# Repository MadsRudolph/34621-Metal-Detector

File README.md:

<div align="center">

# VLF Metal Detector

**Electromagnetic Sensors & Digital Signal Processing**

_A technical implementation of a VLF induction balance metal detector using real-time DFT-based phase detection._

---

</div>

## Overview

This project targets the development of a functional VLF metal detector built on the ATmega328P. It features modular firmware, IIR signal smoothing, and phase-based classification to distinguish between ferromagnetic and non-ferromagnetic metals.

### Features

- **DSP Core:** Single-bin DFT optimized for 4x oversampling (8 kHz) with real-time phase observation.
- **Power Stage:** High-efficiency H-bridge MOSFET driver for the transmitter coil.
- **Coil System:** Concentric coil design with an integrated bucking coil for balance.
- **Feedback:** Real-time OLED HUD and variable-tone buzzer for proximity detection.

## Architecture

```mermaid
graph LR
    MCU[MCU / 2kHz SQ] --> HB[H-Bridge] --> TX[TX Coil]
    Target((Metal)) -. Induction .-> RX[RX Coil]
    RX --> AMP[RX Amp] --> ADC[10-bit ADC]
    ADC --> DFT[DFT Processing] --> IIR[IIR Filter] --> UI[OLED + Buzzer]
```

## Specifications

| Component        | Specification                     |
| :--------------- | :-------------------------------- |
| **TX Frequency** | 2 kHz (Square Wave)               |
| **Sample Rate**  | 8 kHz (4x Oversampling)           |
| **MCU**          | ATmega328P (Arduino Nano @ 16MHz) |
| **Driver**       | H-Bridge (IRF5305 + IRL530)       |
| **Sensors**      | Concentric Coils (Bucking config) |
| **UI**           | SSD1306 OLED (I2C)                |

## Repository

- `Code/` — Core firmware (PlatformIO, C)
- `Docs/` — Technical reports and [Final PDF](Docs/Metaldetektor_Projekt.pdf)
- `KiCad/` — Hardware schematics and PCB designs
- `Simulation/` — LTspice and QSPICE validation files
- `Scripts/` — MATLAB and Python analysis tools

## Getting Started

Build and upload using [PlatformIO](https://platformio.org/):

```bash
cd Code
pio run -t upload
pio device monitor
```

---

<div align="center">
<b>Mads Rudolph · Andreas Skaaning · Jonas Beck · Sigurd Hestbech</b>
<br>
<sub>DTU Course 34621 · January 2026</sub>
</div>

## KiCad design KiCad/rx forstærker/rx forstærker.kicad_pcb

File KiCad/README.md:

# KiCad Skemaer & PCB

Hardware designfiler til VLF Metaldetektoren.

> **Teori:** [Op-Amp Design](obsidian://open?vault=Obsidian&file=Courses%2FIntegrated%20Analog%20Electronics%2FLTspice%20%26%20Kicad%2F02%20-%20Two-Stage%20CMOS%20Op-Amp) | [Induktans](obsidian://open?vault=Obsidian&file=Courses%2FElectromagnetics%2FFormulas%2FL23%20-%20Magnetostatics%20II)

## Status

| Del | Status | Noter |
|-----|--------|-------|
| TX H-bro Driver | ✅ Designet | QSPICE valideret, ~90% effektivitet |
| RX Forstærker | ⏳ Afventer | Design påbegyndt |
| Strømforsyning | ⏳ Afventer | 9V → 5V regulering |
| MCU Sektion | ⏳ Afventer | Arduino Nano breakout |

## Kredsløbsblokke

### 1. Strømforsyning
- 9V batteri input
- Spændingsregulering (5V til MCU)
- Power filtrering
- Batteri monitorering (valgfri)

### 2. TX H-bro Driver
- PWM input fra Arduino (Pin 9)
- **P-kanal MOSFET:** IRF5305PbF (2 stk)
- **N-kanal MOSFET:** IRL530 (2 stk)
- Gate drivere til niveau-skift
- Spoletilslutning (skrueterminal)
- **Effektivitet:** ~90% (QSPICE verificeret)

### 3. RX Forstærker
- Høj-impedans indgangstrin
- Forstærkertrin (op-amp)
- Båndpasfilter omkring 2kHz
- Output skalering til 0-5V for ADC

### 4. Microcontroller Sektion
- Arduino Nano (ATmega328P)
- Intern 10-bit ADC (ingen ekstern ADC nødvendig)
- Timer0 auto-trigger til synkroniseret sampling

### 5. Display & UI
- SSD1306 OLED header (I2C)
- Knapinput (Start/Stop, Kalibrering, Debug)
- Summer output (valgfri)

## Komponentvalg

| Komponent | Delnummer | Pakke | Noter |
|-----------|-----------|-------|-------|
| MCU | Arduino Nano | - | ATmega328P @ 16MHz |
| P-MOSFET | IRF5305PbF | TO-220 | H-bro højside |
| N-MOSFET | IRL530 | TO-220 | H-bro lavside |
| Op-Amp | LM358 / TL072 | DIP-8 | Dual |
| Regulator | 7805 | TO-220 | 5V 1A |
| OLED | SSD1306 | - | 128×64, I2C |

## Pin Mapping (Arduino Nano / ATmega328P)

| Funktion | Arduino Pin | ATmega Pin | Port |
|----------|-------------|------------|------|
| TX Output | 9 | PB1 (15) | PORTB |
| RX Input (ADC) | A0 | PC0 (23) | PORTC |
| I2C SDA | A4 | PC4 (27) | PORTC |
| I2C SCL | A5 | PC5 (28) | PORTC |
| Debug Knap | 4 | PD4 (6) | PORTD |
| Start/Stop | 2 | PD2 (4) | PORTD |
| Kalibrering | 3 | PD3 (5) | PORTD |

## Design Regler (2-lags PCB)

| Parameter | Værdi |
|-----------|-------|
| Min sporbredde | 0.25mm (10mil) |
| Min afstand | 0.25mm (10mil) |
| Via diameter | 0.8mm |
| Via boring | 0.4mm |
| Kobbertykkelse | 1oz |

## Tjekliste

- [x] H-bro design færdigt
- [x] QSPICE simulering bekræftet
- [ ] Skematisk capture komplet
- [ ] ERC (Electrical Rules Check) bestået
- [ ] Footprints tildelt
- [ ] PCB layout komplet
- [ ] DRC (Design Rules Check) bestået
- [ ] Gerbers genereret
- [ ] BOM eksporteret

## Relaterede Dokumenter

- [TX Driver Design.md](../Docs/Theory/TX%20Driver%20Design.md) - H-bro designanalyse
- [Power Budget Analysis.md](../Docs/Theory/Power%20Budget%20Analysis.md) - Strømforbrugsanalyse
- [[../Literature/kravspecifikation.pdf|Kravspecifikation]]

#kicad #pcb #hardware #skema

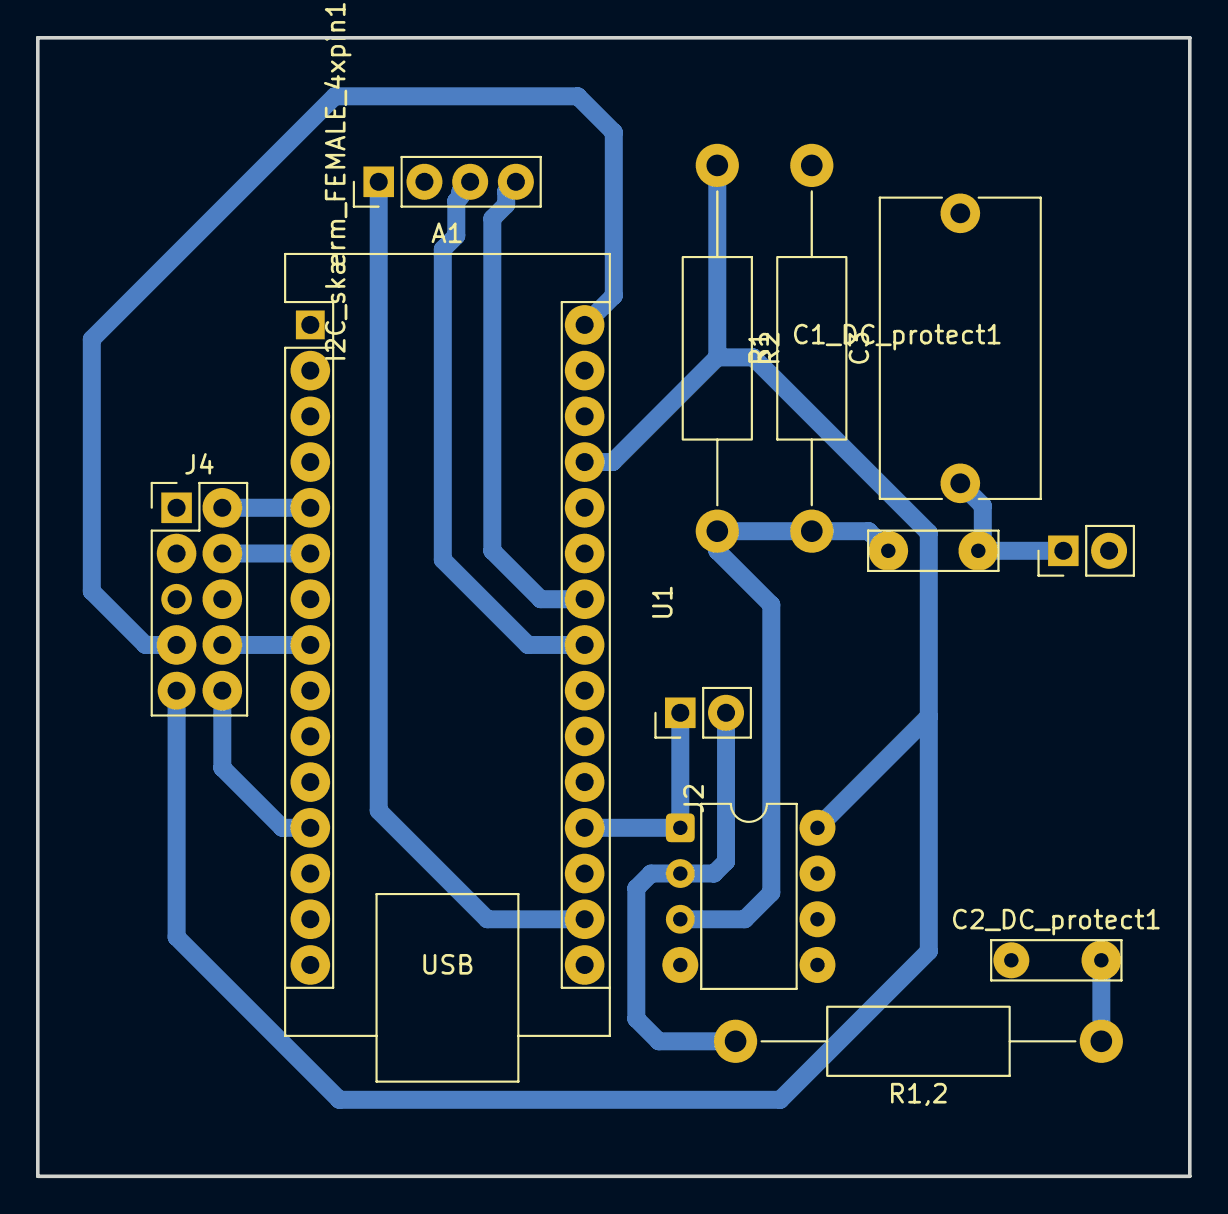
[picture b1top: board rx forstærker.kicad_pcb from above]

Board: 2 copper layers, 64.0 x 63.2 mm, 12 parts (0 on the bottom side), 15 nets.

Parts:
A1: Arduino_Nano
C1_DC_protect1: 1u; C_Rect_L7.0mm_W2.0mm_P5.00mm
C2_DC_protect1: C; C_Rect_L7.0mm_W2.0mm_P5.00mm
C3: 150n; C_Rect_L16.5mm_W8.7mm_P15.00mm_MKT
I2C_skærm_FEMALE_4xpin1: Conn_01x04_Pin; PinHeader_1x04_P2.54mm_Vertical
J1: Rx spole; PinHeader_1x02_P2.54mm_Vertical
J2: Pot_pins_2xpin; PinHeader_1x02_P2.54mm_Vertical
J4: MALE Headers 5xpin; PinHeader_2x05_P2.54mm_Vertical
R1, R2: 100k; R_Axial_DIN0411_L9.9mm_D3.6mm_P20.32mm_Horizontal
R1,2: 1000; R_Axial_DIN0411_L9.9mm_D3.6mm_P20.32mm_Horizontal
U1: MCP6002-xMC; DIP-8_W7.62mm

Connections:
+5V: A1.27 (+5V), J4.9, R2.1, U1.8 (V+)
+9V: A1.30 (VIN), J4.7
/2.5V: C1_DC_protect1.2, R1.1, R2.2, U1.3
/Kalibrering: A1.6 (D3), J4.4
/PA_power_off: A1.8 (D5), J4.8
/Rx_ADC: A1.19 (A0), J2.1, U1.1
/SCL: A1.24 (A5), I2C_skærm_FEMALE_4xpin1.4
/SDA: A1.23 (A4), I2C_skærm_FEMALE_4xpin1.3
/Start/Stop: A1.5 (D2), J4.2
/TX_out->PA: A1.12 (D9), J4.10
/Vin: A1.17 (3V3), I2C_skærm_FEMALE_4xpin1.1
/rx spole. 12.225mH og 71 ohm: C1_DC_protect1.1, C3.1, J1.1
GND: A1.4 (GND), A1.29 (GND), C2_DC_protect1.1, C3.2, I2C_skærm_FEMALE_4xpin1.2, J4.1, J4.3, R1.2, U1.4 (V-)
unnamed: C2_DC_protect1.2, R1,2.1
unnamed: J2.2, R1,2.2, U1.2

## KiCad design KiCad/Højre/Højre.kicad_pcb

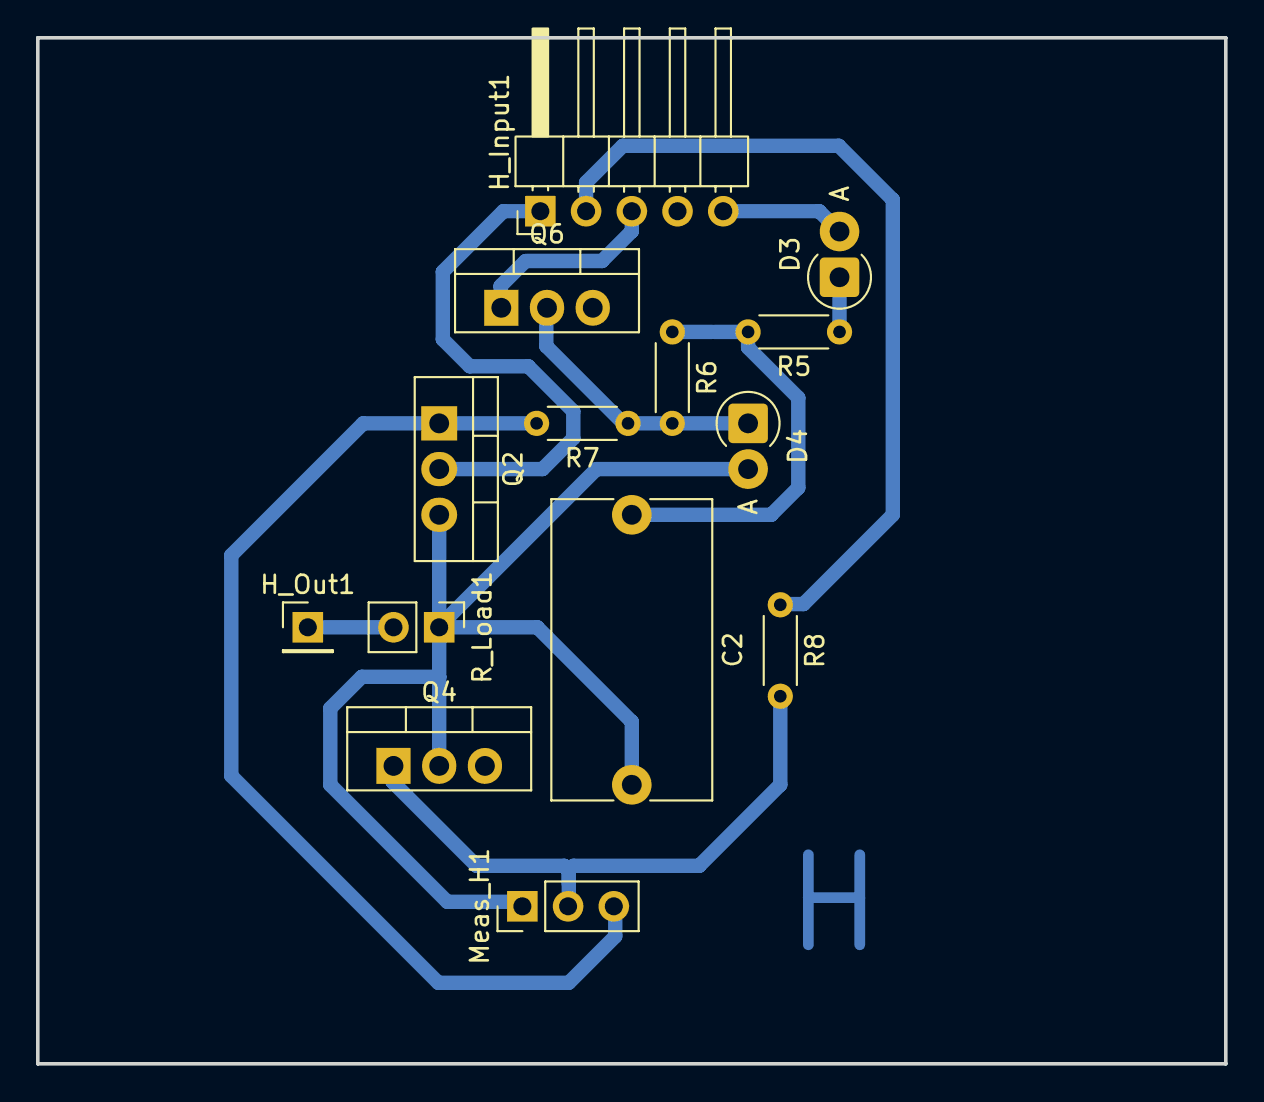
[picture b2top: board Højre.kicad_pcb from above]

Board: 2 copper layers, 66.0 x 57.0 mm, 14 parts (0 on the bottom side), 12 nets.

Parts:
C2: 820n; C_Rect_L16.5mm_W8.7mm_P15.00mm_MKT
D3, D4: D; D_DO-41_SOD81_P2.54mm_Vertical_AnodeUp
H_Input1: Conn_01x05_Pin; PinHeader_1x05_P2.54mm_Horizontal
H_Out1: Conn_01x01_Pin; PinHeader_1x01_P2.54mm_Vertical
Meas_H1: Conn_01x03_Pin; PinHeader_1x03_P2.54mm_Vertical
Q2, Q4, Q6: NMOS_IRL530; TO-220-3_Vertical
R5, R7, R8: 1; R_Axial_DIN0204_L3.6mm_D1.6mm_P5.08mm_Horizontal
R6: 1k; R_Axial_DIN0204_L3.6mm_D1.6mm_P5.08mm_Horizontal
R_Load1: 47; PinHeader_1x02_P2.54mm_Vertical

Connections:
+5V: D3.2 (A), H_Input1.5
+9V: H_Input1.1, Q2.2 (G)
/Meas_GATE_M2: Meas_H1.3, Q2.1 (D), R7.2
/Meas_GATE_M4: Meas_H1.2, Q4.1 (D), R8.2
/Meas_H_Out: C2.2, D4.2 (A), Meas_H1.1, Q2.3 (S), Q4.2 (G), R_Load1.1
/PWM1_NOT: H_Input1.3, Q6.1 (D)
/PWM2: H_Input1.2, R8.1
GND: H_Input1.4, Q4.3 (S), Q6.3 (S)
unnamed: C2.1, R5.2, R6.1
unnamed: D3.1 (K), R5.1
unnamed: D4.1 (K), Q6.2 (G), R6.2, R7.1
unnamed: H_Out1.1, R_Load1.2

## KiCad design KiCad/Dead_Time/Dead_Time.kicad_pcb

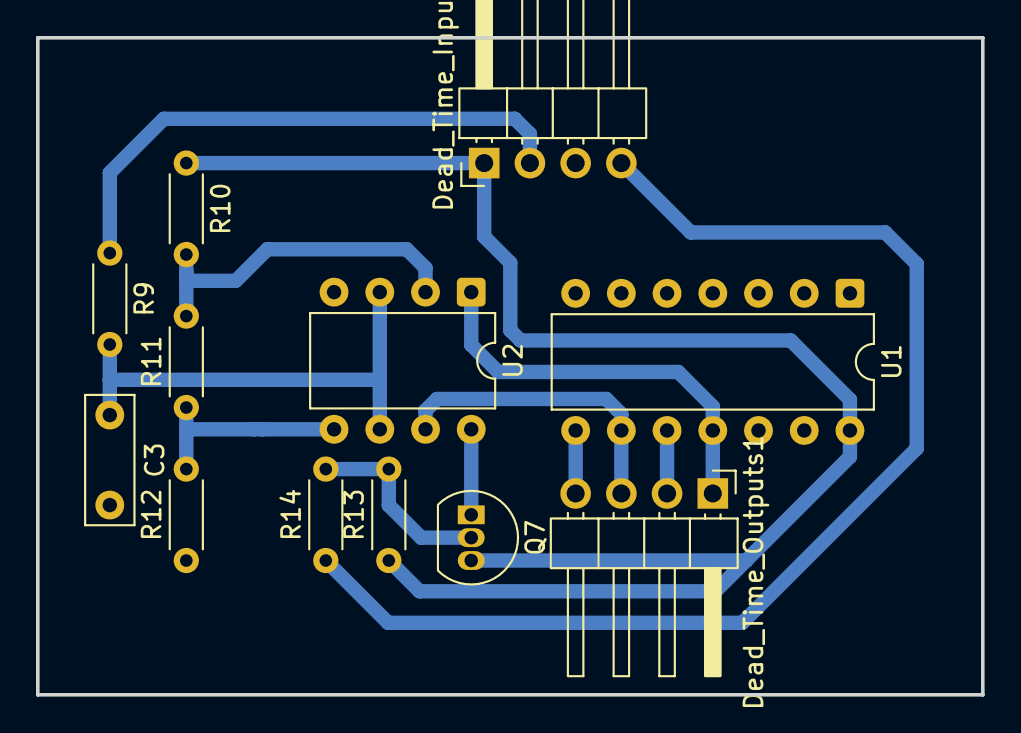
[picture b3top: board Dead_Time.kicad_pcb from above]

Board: 2 copper layers, 52.5 x 36.5 mm, 12 parts (0 on the bottom side), 13 nets.

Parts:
C3: 4n8; C_Rect_L7.0mm_W2.5mm_P5.00mm
Dead_Time_Inputs1: Conn_01x04_Pin; PinHeader_1x04_P2.54mm_Horizontal
Dead_Time_Outputs1: Conn_01x04_Pin; PinHeader_1x04_P2.54mm_Horizontal
Q7: PNP_BC558; TO-92_Inline
R9: 15k; R_Axial_DIN0204_L3.6mm_D1.6mm_P5.08mm_Horizontal
R10, R12: 2k25; R_Axial_DIN0204_L3.6mm_D1.6mm_P5.08mm_Horizontal
R11: 500; R_Axial_DIN0204_L3.6mm_D1.6mm_P5.08mm_Horizontal
R13: 10k; R_Axial_DIN0204_L3.6mm_D1.6mm_P5.08mm_Horizontal
R14: 1k; R_Axial_DIN0204_L3.6mm_D1.6mm_P5.08mm_Horizontal
U1: 74AUC2G04; DIP-14_W7.62mm
U2: MCP6002; DIP-8_W7.62mm

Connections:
+5V: Dead_Time_Inputs1.1, Q7.3 (E), R10.1, R13.1, U1.14
/KILL_SWITCH: Q7.1 (C), U2.8 (V+)
/Meas_VStep1: R10.2, R11.2, U2.2 (-)
/Meas_VStep2: R11.1, R12.2, U2.5 (+)
/PWM1: Dead_Time_Outputs1.1, U1.11, U2.1
/PWM1_NOT: Dead_Time_Outputs1.2, U1.10
/PWM2: Dead_Time_Outputs1.3, U1.9, U2.7
/PWM2_NOT: Dead_Time_Outputs1.4, U1.8
/PWM_In: Dead_Time_Inputs1.2, R9.1
/on/off: Dead_Time_Inputs1.4, R14.1
GND: C3.2, Dead_Time_Inputs1.3, R12.1, U1.7, U2.4 (V-)
unnamed: Q7.2 (B), R13.2, R14.2
unnamed: C3.1, R9.2, U2.3 (+), U2.6 (-)

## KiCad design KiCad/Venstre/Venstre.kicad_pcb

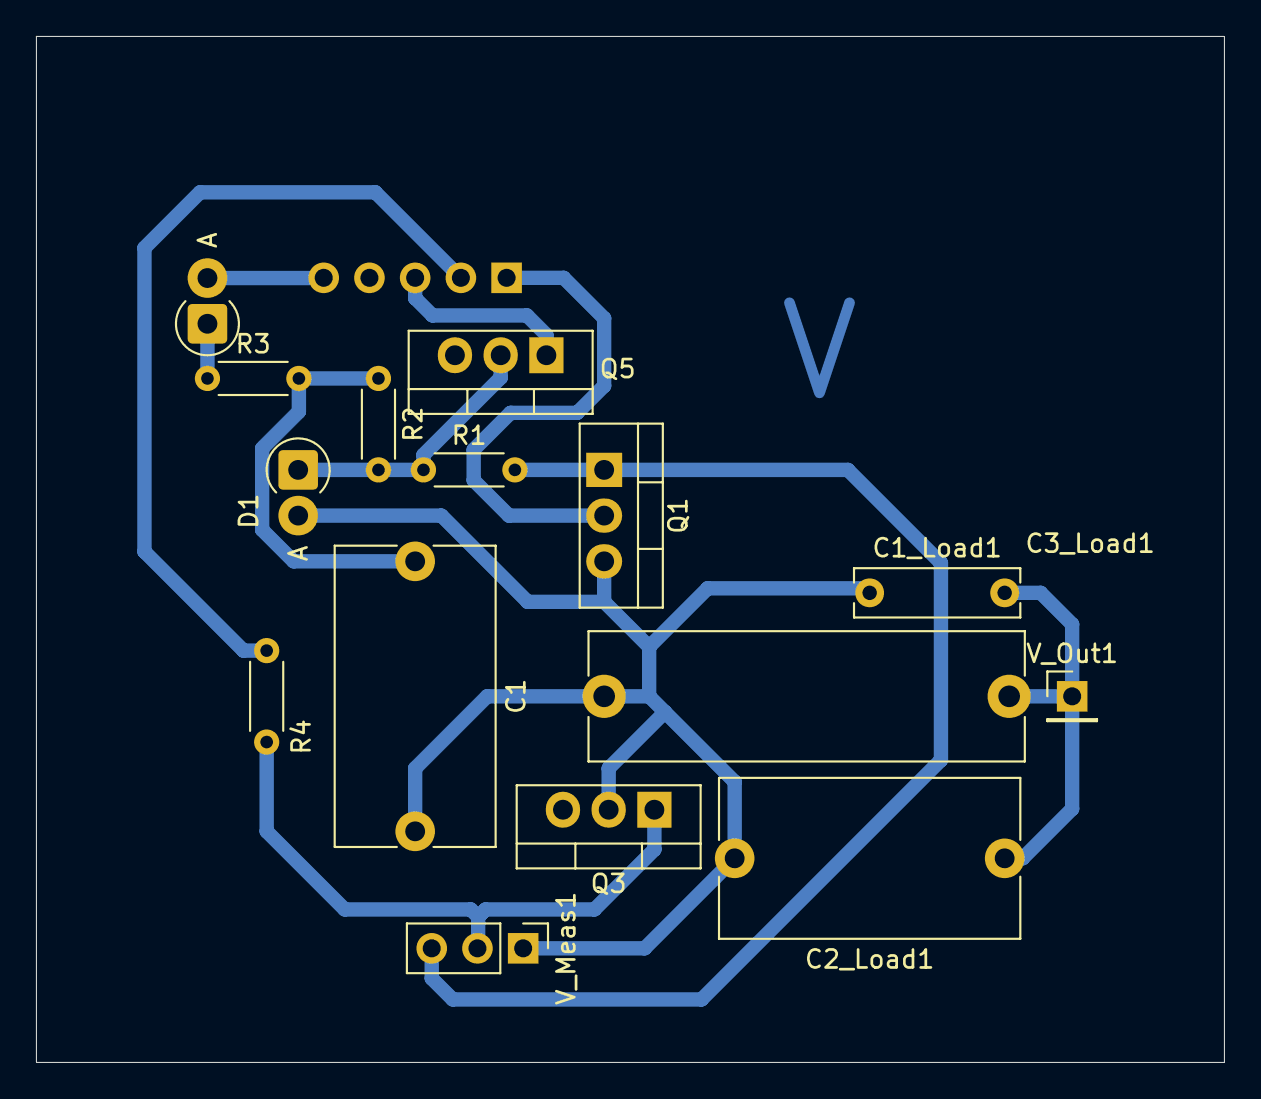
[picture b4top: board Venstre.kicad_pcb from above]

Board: 2 copper layers, 66.0 x 57.0 mm, 16 parts (1 on the bottom side), 12 nets.

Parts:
C1, C2_Load1: 820n; C_Rect_L16.5mm_W8.7mm_P15.00mm_MKT
C1_Load1: 100n; C_Rect_L9.0mm_W2.5mm_P7.50mm_MKT
C3_Load1: 2u2; C_Rect_L24.0mm_W7.0mm_P22.50mm_MKT
D1, D2: D; D_DO-41_SOD81_P2.54mm_Vertical_AnodeUp
Q1, Q3, Q5: NMOS_IRL530; TO-220-3_Vertical
R1, R3, R4: 1; R_Axial_DIN0204_L3.6mm_D1.6mm_P5.08mm_Horizontal
R2: 1k; R_Axial_DIN0204_L3.6mm_D1.6mm_P5.08mm_Horizontal
V_Inputs1: Conn_01x05_Pin; PinHeader_1x05_P2.54mm_Horizontal
V_Meas1: Conn_01x03_Pin; PinHeader_1x03_P2.54mm_Vertical
V_Out1: Conn_01x01_Pin; PinHeader_1x01_P2.54mm_Vertical

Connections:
+5V: D2.2 (A), V_Inputs1.5
+9V: Q1.2 (G), V_Inputs1.1
/Meas_GATE_M1: Q1.1 (D), R1.2, V_Meas1.3
/Meas_GATE_M3: Q3.1 (D), R4.2, V_Meas1.2
/Meas_V_Out: C1.2, C1_Load1.1, C2_Load1.2, C3_Load1.1, D1.2 (A), Q1.3 (S), Q3.2 (G), V_Meas1.1
/PWM1: R4.1, V_Inputs1.2
/PWM2_NOT: Q5.1 (D), V_Inputs1.3
GND: Q3.3 (S), Q5.3 (S), V_Inputs1.4
unnamed: C1.1, R2.1, R3.2
unnamed: D1.1 (K), Q5.2 (G), R1.1, R2.2
unnamed: D2.1 (K), R3.1
unnamed: C1_Load1.2, C2_Load1.1, C3_Load1.2, V_Out1.1

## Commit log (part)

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2026-01-05 Initial commit: VLF Metal Detector project
2026-01-05 added crosslink to DTU Obsidian Vault
2026-01-06 ingenting
2026-01-06 added maple
2026-01-06 Created power_test.c to test current draw on Arduino Mega
2026-01-06 Lavet lidt udregner i Maple, de skal kigges mere på
2026-01-07 Simplify to prime number calculator test program
    Replace complex metal detector firmware with simple prime calculator
    that displays results on OLED. Removes unused DSP, sampling, TX, and
    UART modules to measure baseline power consumption.
2026-01-07 Mutual inductance added
2026-01-07 B-fields added
2026-01-07 Power Budget code works, documented findings and updated power budget analysis.md, preparing to merge back into main branch
2026-01-07 Add power_test directory with power budget test code
    Merged code from Powerbudget branch as a separate directory to allow
    running power consumption tests independently from the main detector code.
    Includes Power Budget Analysis documentation.
2026-01-07 made a plan for code execution, and updated Power budget analysis
2026-01-07 Skabelon til coiludregninger
2026-01-07 Update .gitignore and untrack generated files
    Remove workspace.json, nested .vscode folders, .claude settings, and
    build artifacts from tracking to prevent merge conflicts when switching
    branches. These files are machine/user-specific and shouldn't be shared.
2026-01-07 Add debug system and complete firmware implementation
    Debug System:
    - debug.h/debug.c: 4-screen diagnostic system (ADC, DFT Accum, DFT Result, Timing)
    - Integer math: isqrt(), fast_atan2_deg() for embedded constraints
    - Pin 13 toggle for oscilloscope timing verification
    - Activate by holding both buttons in IDLE state
    Firmware:
2026-01-08 Add Arduino Nano (ATmega328P) support
    Implement portable firmware supporting both Arduino Mega 2560 and Nano:
    - config.h: Board detection with conditional pin/timer definitions
    - tx.c: Use config macros for TX PWM pin (PB5 on Mega, PB1 on Nano)
    - ui.c: Timer4 (Mega) / Timer2 (Nano) buzzer, portable button handling
    - main.c: Use BTN_PIN macros for button reading
    - debug.h/c: Include config.h for debug pin (PB7 on Mega, PB0 on Nano)
2026-01-08 QSPICE sim virker ca 90% effektiv
2026-01-08 Created matlab simulation of coil design
2026-01-08 opdateret maple
2026-01-08 referat fra møde 8-1-26
2026-01-08 Timer 0
2026-01-09 Port migration branch logic with bug fixes applied
    - Simplified DSP/TX code using migration branch style
    - Fixed OCR0A: 124 -> 249 for correct 8kHz interrupt rate
    - Fixed types: xn as int16_t for signed DC offset result
    - Replaced floating-point sqrt/atan2 with integer-only versions
    - Using auto-trigger ADC (ADATE) instead of manual triggering
    - Added proper header declarations and function prototypes
2026-01-09 made a simple test program with everything in main.c no sub .c documents or header files
2026-01-09 simple main is now the main code branch
2026-01-09 fixede timer0
2026-01-09 📝 Add docstrings to `simplemain`
    Docstrings generation was requested by @MadsRudolph.
    * https://github.com/MadsRudolph/34621-Metal-Detector/pull/11#issuecomment-3730168718
    The following files were modified:
    * `Code/src/drivers/I2C.c`
    * `Code/src/main.c`
2026-01-09 Add Coil Configuration Comparison from Powerbudget branch
2026-01-09 Add Maple coil design document
2026-01-09 Reorganize documentation: new Docs/ structure, delete outdated files
    - Created Docs/Guides, Docs/Theory, Docs/Meetings, Docs/Templates
    - Moved all documentation to appropriate folders
    - Deleted outdated: Debug_Guide.md, Development Roadmap.md, Search Coil Design.md
    - Renamed Coil_Design_Reconciliation.md to Coil Design.md
    - Updated Home.md with new links and current architecture
2026-01-10 Major documentation overhaul and firmware cleanup
    Project Roadmap & Requirements:
    - Add Project_Roadmap.md with full requirements analysis (16 krav)
    - Map implementation status: ~45% complete (SW 70%, HW 30%)
    - Document outstanding tasks, risks, and test checklist
    Firmware (main.c):
    - Restructure with clear section headers and organization
2026-01-10 Add push-pull driver design and efficiency analysis to TX Driver docs
    - Add new push-pull (totem-pole) driver circuit with 5 BJTs
    - Add ASCII schematics and component list for push-pull design
    - Add H-bridge vs push-pull comparison table
    - Add efficiency and battery consumption analysis section
    - Add detailed battery life calculations (174 min vs 271 min)
    - Add build instructions, wiring guide, and test procedures
2026-01-10 Add report export system for Overleaf integration
    - Report_Export/ folder for staging assets (figures, schematics, code, data)
    - export_to_report.sh script to sync assets to report repository
    - README with workflow and naming conventions
2026-01-11 Hbro done 98% effektivitet
2026-01-11 opdateret RLC filter som giver pæn sinus
2026-01-12 Add QSPICE simulation documentation
    Document the H-bridge TX driver simulation files:
    - Hbro_sim.qsch: Main H-bridge with IRL530 MOSFETs and LC tank (~98% efficiency)
    - bootstrap.qsch: Bootstrap gate driver for high-side N-channel drive
    - dead_time.qsch: RC-based dead-time generator using op-amp comparators
    Includes circuit topology, component specifications, operating principles,
    and simulation commands for parameter sweeps.
2026-01-12 Address review comments for QSPICE documentation
    - Add 'text' language specifier to ASCII diagram code blocks for
    proper markdown rendering
    - Document R4/R8 (1K) pull-up resistors in Bootstrap Components table
    - Add explanation for pull-up resistor function
2026-01-12 Consolidate and restructure documentation
    Documentation reduced from 18 to 14 files by merging redundant content:
    New files:
    - Docs/Guides/Testing Guide.md - Unified test guide (AD3, RC Loopback, MATLAB DFT)
    - Docs/Theory/TX Driver Design.md - H-bridge driver theory
    Merged and deleted:
    - Coil Configuration Comparison.md -> merged into Coil Design.md
2026-01-12 Add coil winder project and documentation
    - Add complete coil winder firmware with Doxygen documentation
    - ATmega328P-based controller for automated coil winding
    - Servo-controlled wire guide with encoder feedback
    - SSD1306 OLED display interface
    - Configurable coil presets for TX/RX coils
    - 3D printable mechanical parts (OpenSCAD)
2026-01-13 Replace ITR8307 reflective sensor with break-beam optical sensor
    - New sensor design using SFH4546 IR emitter + BP104 photodiode + LM311 comparator
    - All components available from DTU component shop
    - More reliable detection using slotted encoder disc instead of reflective stripe
    - Updated circuit schematics, component calculations, and wiring diagrams
    - Added DTU component shop inventory CSV for reference
2026-01-13 Fix Wheeler inductance formula and update coil design documentation
    - Fix Wheeler formula coefficient: 0.8 (inches) -> 0.315 (cm)
    - Add single-layer Wheeler formula for bucking coil
    - Add geometry warning for flat TX coil
    - Update MATLAB script with verified formulas
    - Update coil specifications based on corrected calculations
    - Update power budget for 360mA TX current
2026-01-15 Enkelte QSPICE ændringer plus kicad schematik af Hbro
2026-01-15 ændret kicad opsætning
2026-01-15 Update Coil Design with measured values
    - TX+Bucking series: 2.03 mH (vs 5.82 mH theoretical)
    - RX inductance: 12.25 mH (0.4% error from theory)
    - Bucking coil optimal: 20 turns (removed 15 from 35)
2026-01-15 Update coil specs with verified measurements from verify_coils.m
    Actual specifications:
    - TX: 70 turns, 2 layers, 200mm, 0.56mm wire → 1.97 mH
    - Bucking: 20 turns, 1 layer, 60mm, 0.56mm wire → 0.038 mH
    - RX: 445 turns, 3 layers, 50mm, 0.15mm wire → 11.1 mH
    Verification results:
    - TX+Bucking: 2.01 mH theoretical vs 2.03 mH measured (-0.9% error)
2026-01-15 Update coil design with prototype simulation values
    - TX: 70 turns, 2 layers, 1.97 mH, 3.02Ω DC
    - RX: 445 turns, 3 layers, 11.15 mH, 67.05Ω DC
    - Bucking: 20 turns calibrated, 0.04 mH, 0.26Ω DC
    - Updated resonance calculations and overview tables
    - MATLAB script now uses actual prototype values
2026-01-16 nyste pcb design til AP forstærker
2026-01-16 alla pcber er klar til routing
2026-01-16 deadtime pcb almost done, missing 1 gnd connection
2026-01-16 Venstre og Højre pcb klar til produktion
2026-01-16 midlertidig backup før branch skift
2026-01-17 niger
2026-01-17 pcb layouts done
2026-01-17 Remove Doxygen-generated HTML documentation
    Delete auto-generated documentation files from Code/docs/html
    and coil_winder/docs/html directories.
2026-01-17 Add tmpclaude-* to gitignore
2026-01-17 Re-enable MATLAB capture code
2026-01-18 sleep + rx forstærker i LT
2026-01-18 RX forstærker + MCU i kicad, mangler footprints
2026-01-18 rxforstærker simplificeret
2026-01-18 Modulariser kode og tilføj buzzer feedback
    Opdeler main.c i separate moduler for bedre læsbarhed:
    - config.h: Alle konfigurationskonstanter
    - timer: TX signal generation og sleep mode
    - adc: 8kHz ADC sampling
    - button: Knap håndtering
    - dft: DFT beregning
2026-01-19 Ret metal klassificering og tilføj sleep pin styring
    - Ret ferro/non-ferro klassificering (positiv fase = ferro, negativ = non-ferro)
    - Sænk magnitude tærskel for bedre følsomhed (20% eller +3)
    - Tilføj SLEEP_PIN (PD5) til at styre forstærker sleep mode
    - Gør signal bar mere følsom (bar_max 200 → 50)
2026-01-19 Add graphical HUD display with icons and startup sound
    - Graphical progress bar and large percentage numbers on display
    - Metal type icons (ferro, non-ferro, searching)
    - Splash screen with DTU 34621 branding at startup
    - Startup jingle (rising power-up sound)
    - Simplified buzzer to beeps that increase with signal strength
    - Reduced display flicker by only redrawing changed elements
2026-01-19 Move header files to include folder
    - Created src/include/ folder for all header files
    - Updated all #include paths in .c files accordingly
    - Cleaner separation between headers and source files
2026-01-19 lavet pcb design til arduino/Rx forstærker
2026-01-19 Update power budget with actual measurements (56 mA)
    - Add verified measurements: 56 mA total system current
    - Document sleep mode implementation (PD5 → H-bridge enable)
    - H-bridge duty-cycled at ~50% via Timer1 interrupt
    - MCU enters idle mode when H-bridge sleeps
    - Runtime: ~550 min (9 hours), exceeds 100 min requirement by 5.5×
2026-01-19 Add H-bridge power control to start/stop button
    When detection is stopped, PD5 is held HIGH permanently to disable
    the H-bridge. Timer1 ISR now checks detection_active before toggling
    SLEEP_PIN, preventing override of the stop state.
2026-01-19 Add battery voltage monitoring (46.3k/10k divider on A1)
    - New battery.c/h module with ADC reading and IIR filtering
    - Display battery voltage on main HUD and debug screen
    - Document voltage divider circuit and expected readings
    - Explain battery voltage drop under load behavior
2026-01-19 Fix ADC race condition in battery_read() and markdown linting
    Disable ADATE and ADIE before switching ADMUX to prevent race with
    auto-triggered conversions. Add text language identifier to ASCII-art
    code fences in Assembly_Guide to satisfy MD040.
2026-01-20 Ready for merge: HTML dashboard improvements only
2026-01-21 Remove MATLAB capture/debug code and reorganize project structure
    - Remove capture.c/capture.h (MATLAB verification interface)
    - Remove debug display mode and D4 button from firmware
    - Update Code_Review.md to reflect changes
    - Move loose files into appropriate folders:
    - Home.md, Test Plans -> Docs/
    - export_to_report.sh -> Scripts/
2026-01-21 Add script to regenerate battery graphs with smoothed voltage curve
    Applies moving average filter to reduce ADC noise in the voltage readings.
    Window size is configurable (default 30 samples).
2026-01-22 Add H-Bridge measurement guide with AD3 oscilloscope captures
    - New Obsidian guide for characterizing H-bridge amplifier
    - Documents 6 tests: deadtime, gate drive, half-bridge output,
    differential output, LC tank current, and RX coil response
    - Includes measurement screenshots demonstrating metal detection
2026-01-23 cleaned up code
2026-01-26 Add final project report and mark project as completed
    - Add Metaldetektor_Projekt.pdf final report
    - Update README to reflect completed status
    - Add battery discharge test image
    - Update power budget analysis
